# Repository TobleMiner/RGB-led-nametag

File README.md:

RGB LED nametag
===============

While there are a few commercially available LED nametags out there they
are usually either monochrome only or far too big and bulky to wear.  
This project aims at designing a device solving that problem.  
At only 84mm wide and 29mm tall it is hardly any larger than normal,
boring paper nametags and packs a whole lot more features:

- WLAN enabled
- 48x16 glorious RGB led pixels with more than 16 million colors each
- Powerful ARM Cortex M7 and Xtensa 32bit dual core
- 3MB of onboard data storage

# Principle of operation

The RGB LEDs on this nametag are common anode LEDs. The LEDs are divided
into groups of 16 columns each. The display is then multiplexed over those
16 columns, always driving one of the 16 columns in each of the three
groups simultaneously. Each of the 3 groups features 48 low side row
drivers driving the R, G and B emitter of all 16 LEDs in the currently
selected column.  
Both the low and high side drivers are designed as shift registers. The
low side drivers are fed with data from a regular SPI while the high side
drivers are connected to a QSPI interface. On the QSPI interface three
of the four data lines are utilized to provide data for all three LED
groups simultaneously.  
Both the SPI and QSPI are peripherals of an STM32F722 MCU. The STM32
takes care of LED multiplexing, power management, user io and USB.  
To provide WLAN connectivity an ESP32 is connected to the STM32 via
an IRQ line, a SPI interface, an I2C interface and a UART. IO0 and EN of
the ESP32 are also connected to the STM32. This allows the STM32 to be
used as a USB to UART bridge allowing normal programming of the ESP32
directly from your favourite IDE.

# Assembly

Since double sided assembly and boards with blind vias tends to be on the
expensive side this project is comprised of four boards. The first one is
the board shown above. The remaining three boards are all the same and
carry 16x16 LEDs each. They need to be soldered back to back onto the
mainboard. Design files for the LED carrier boards can be found
[here](https://github.com/TobleMiner/16x16-RGB-led-panel).

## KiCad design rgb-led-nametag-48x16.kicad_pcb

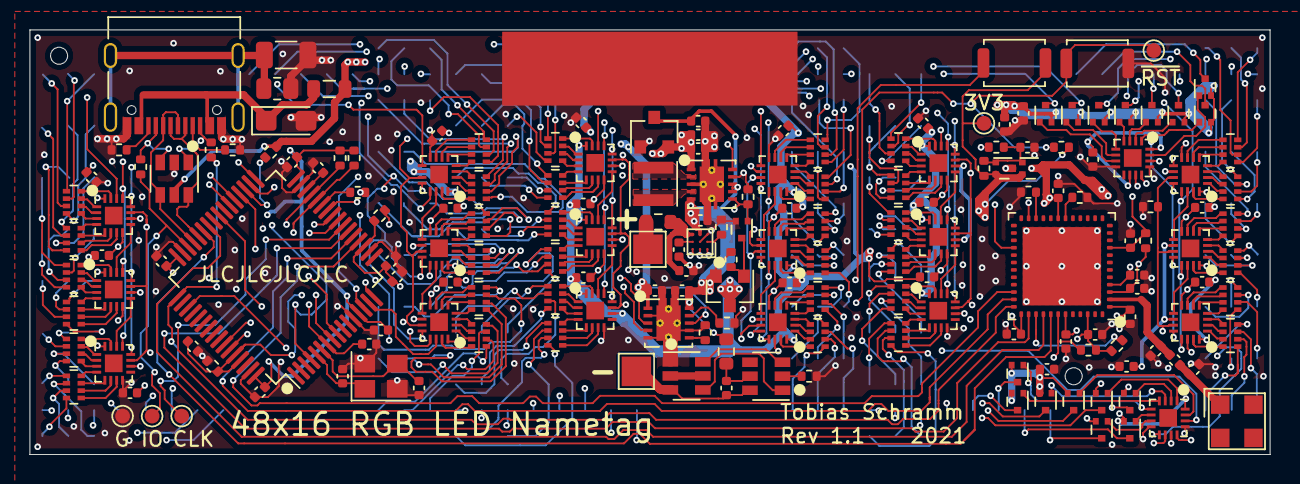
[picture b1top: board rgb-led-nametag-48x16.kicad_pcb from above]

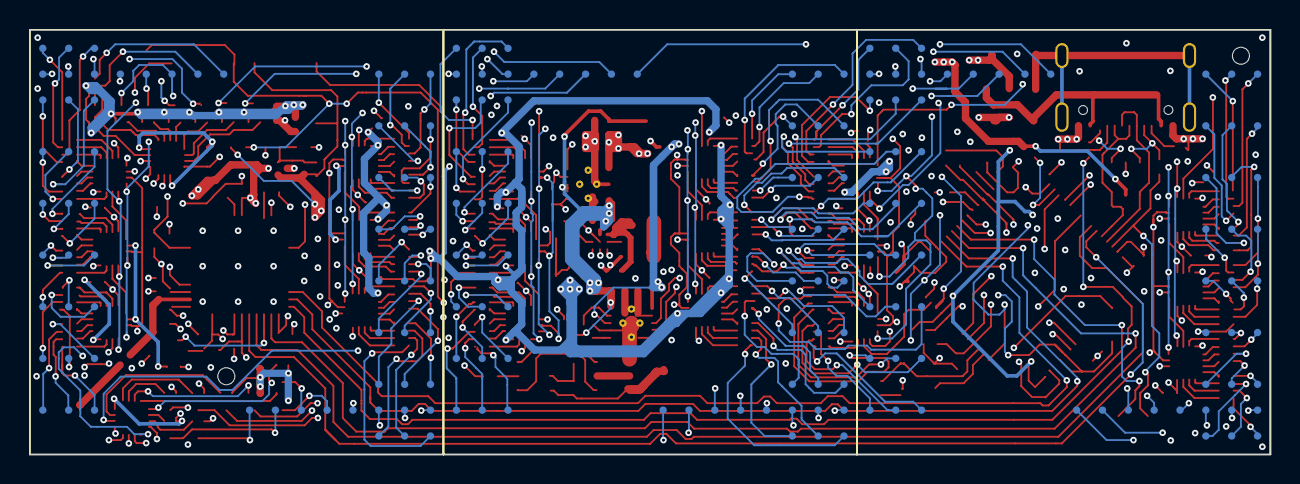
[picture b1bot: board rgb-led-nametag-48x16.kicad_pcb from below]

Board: 4 copper layers, 84.0 x 28.8 mm, 189 parts (3 on the bottom side), 405 nets.

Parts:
AE1: Antenna; 2065130001
C1, C2, C3, C4, C5, C6, C7, C8, C9, C10, C11, C12, C13, C14, C15, C16, C17, C18, C19, C20, C30, C32, C33, C34, C35, C36, C40, C46, C48, C49: 100nF; C_0402_1005Metric
C21, C22, C23, C24, C28, C29, C39, C41, C42, C43, C50, C51, C52: 10uF; C_0402_1005Metric
C25: 0R; C_0402_1005Metric
C26, C27: DNP; C_0402_1005Metric
C31: 4.7uF; C_0402_1005Metric
C37: 1nF; C_1206_3216Metric
C38: 10uF; CP_EIA-3216-10_Kemet-I
C44, C45, C47, C53, C54: 1uF; C_0402_1005Metric
C55, C56: 20pF; C_0402_1005Metric
F1: 4A; R_0603_1608Metric
FB1: Bead; L_0805_2012Metric
H1, H2: ToolingHole; ToolingHole_JLCSMT
H3: Safety pin; MountingPad_20x5mm
J1: USB_C_Receptacle_USB2.0; USB_C_Receptacle_Palconn_UTC16-G
L1: 2.2uH; L_Taiyo-Yuden_MD-3030
Q1, Q2, Q3, Q4, Q5, Q6, Q7, Q8, Q9, Q10, Q11, Q12, Q13, Q14, Q15, Q16, Q17, Q18: CJ3139K; SOT-723
Q19: 2SK3541; SOT-723
Q20: AO3401A; SOT-23
Q21: FS8205A; SOT-23-6
R1, R2, R6, R10, R12: 100k; R_0402_1005Metric
R3: 200k; R_0805_2012Metric
R4, R5, R13, R14, R17, R18, R19, R25, R26: 5.1k; R_0402_1005Metric
R7, R15, R16: 470R; R_0402_1005Metric
R8: 33R; R_0402_1005Metric
R9, R21, R23, R24, R27: 10k; R_0402_1005Metric
R11: 1k; R_0402_1005Metric
R20: 1.5k; R_0402_1005Metric
R22: 470R; R_0603_1608Metric
RN1, RN2, RN3, RN4, RN5, RN6, RN7, RN8, RN9, RN10, RN11, RN12, RN13, RN14, RN15, RN16, RN17, RN18, RN19, RN20, RN21, RN22, RN23, RN24, RN25, RN26, RN27, RN28, RN29, RN30, RN31, RN32, RN33, RN34, RN35, RN36: 220R; R_Array_Concave_4x0402
SW1: DFU/BTN; SW_Push_SPST_NO_Alps_SKRK
SW2: RST; SW_Push_SPST_NO_Alps_SKRK
TP1: BAT+; TestPoint_Pad_2.0x2.0mm
TP2: BAT-; TestPoint_Pad_2.0x2.0mm
TP3: ~{RST}; TestPoint_Pad_D1.0mm
TP4: SWDIO; TestPoint_Pad_D1.0mm
TP5: SWCLK; TestPoint_Pad_D1.0mm
TP6: GND; TestPoint_Pad_D1.0mm
TP7: 3V3; TestPoint_Pad_D1.0mm
U1, U9, U16: led-panel-16x16; bga-led-panel-16x16
U2, U3, U4, U5, U6, U7, U8, U10, U11, U12, U13, U14, U15, U17, U18, U19, U20, U21, U22, U23: 74HC595; X1QFN-16-2.5x2.5-EP-1.2
U24: ESP32-PICO-D4; ESP32-Pico-D4
U25: STM32F722RETx; LQFP-64_10x10mm_P0.5mm
U26: SRV05-4; SOT-23-6
U27: TPS63001; Texas_DRC0010J_ThermalVias
U28: XC6206P332MR; SOT-23
U29: BQ24081; Texas_DRC0010J_ThermalVias
U30: DW01+G; SOT-23-6
U31: BQ27421; DSBGA-9_1.6x1.6_P0.5mm
Y1: 16MHz; Crystal_SMD_3225-4Pin_3.2x2.5mm

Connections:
+3V3: C32.1, C33.2, C34.1, C35.1, C36.1, C42.2, C43.2, C50.1, Q17.2 (S), Q18.2 (S), R1.2, R10.2, R25.2, R26.1, R27.2, SW1.2, TP7.1, U25.13 (VREF+), U25.19 (VDD), U25.32 (VDD), U25.48 (VDD), U25.64 (VDD), U27.1 (VOUT), U27.10 (FB), U28.2 (VO)
+5V: C47.1, FB1.1, R23.2, U26.5 (VP), U29.1 (IN), U29.8 (~TE)
+BATT: C41.2, C44.1, C48.2, Q20.2 (S), R12.1, R22.1, U27.5 (VIN), U27.7 (PS/SYNC), U27.8 (VINA), U28.3 (VI), U29.10 (OUT), U31.C2 (SRX)
/A1: Q1.3 (D), U1.B1 (A1), U9.B1 (A1), U16.B1 (A1)
/A2: Q2.3 (D), U1.B2 (A2), U9.B2 (A2), U16.B2 (A2)
/A3: Q3.3 (D), U1.B3 (A3), U9.B3 (A3), U16.B3 (A3)
/A4: Q4.3 (D), U1.B4 (A4), U9.B4 (A4), U16.B4 (A4)
/A5: Q5.3 (D), U1.B5 (A5), U9.B5 (A5), U16.B5 (A5)
/A6: Q6.3 (D), U1.B6 (A6), U9.B6 (A6), U16.B6 (A6)
/A7: Q7.3 (D), U1.B7 (A7), U9.B7 (A7), U16.B7 (A7)
/A8: Q8.3 (D), U1.B8 (A8), U9.B8 (A8), U16.B8 (A8)
/A9: Q9.3 (D), U1.R9 (A9), U9.R9 (A9), U16.R9 (A9)
/A10: Q10.3 (D), U1.R10 (A10), U9.R10 (A10), U16.R10 (A10)
/A11: Q11.3 (D), U1.R11 (A11), U9.R11 (A11), U16.R11 (A11)
/A12: Q12.3 (D), U1.R12 (A12), U9.R12 (A12), U16.R12 (A12)
/A13: Q13.3 (D), U1.R13 (A13), U9.R13 (A13), U16.R13 (A13)
/A14: Q14.3 (D), U1.R14 (A14), U9.R14 (A14), U16.R14 (A14)
/A15: Q15.3 (D), U1.R15 (A15), U9.R15 (A15), U16.R15 (A15)
/A16: Q16.3 (D), U1.R16 (A16), U9.R16 (A16), U16.R16 (A16)
/BOOT: U24.23 (IO0), U25.25 (PB0)
/COL_LATCH: U8.12 (RCLK), U23.12 (RCLK), U25.14 (PA0)
/D+: J1.A6 (D+), J1.B6 (D+), U25.45 (PA12), U26.4 (IO3)
/D-: J1.A7 (D-), J1.B7 (D-), U25.44 (PA11), U26.6 (IO4)
/DFU: C46.1, R2.2, SW1.1, U25.60 (BOOT0), U25.61 (PB8)
/EN: C40.1, R6.1, U24.9 (EN), U25.26 (PB1)
/GAUGE_SCL: R25.1, U25.28 (PB10), U31.A3 (SCL)
/GAUGE_SDA: R26.2, U25.29 (PB11), U31.A2 (SDA)
/GPOUT: R27.1, U25.9 (PC1), U31.A1 (GPOUT)
/High side 1/SOUT: U8.9 (QH'), U23.14 (SER)
/IRQ: U24.28 (SD2/IO9), U25.24 (PC4)
/L1: L1.1, U27.4 (L1)
/L2: L1.2, U27.2 (L2)
/PWR_EN: Q19.1 (G), R9.1, U25.4 (PC15), U27.6 (EN)
/Panel 1/B1: RN2.2 (R2.1), U1.A3 (B1)
/Panel 1/B2: RN11.3 (R3.1), U1.B16 (B2)
/Panel 1/B3: RN1.3 (R3.1), U1.C3 (B3)
/Panel 1/B4: RN12.2 (R2.1), U1.D16 (B4)
/Panel 1/B5: RN4.4 (R4.1), U1.E3 (B5)
/Panel 1/B6: RN9.1 (R1.1), U1.F16 (B6)
/Panel 1/B7: RN4.1 (R1.1), U1.G3 (B7)
/Panel 1/B8: RN9.4 (R4.1), U1.H16 (B8)
/Panel 1/B9: RN3.2 (R2.1), U1.J3 (B9)
/Panel 1/B10: RN10.3 (R3.1), U1.K16 (B10)
/Panel 1/B11: RN6.3 (R3.1), U1.L3 (B11)
/Panel 1/B12: RN7.2 (R2.1), U1.M16 (B12)
/Panel 1/B13: RN5.4 (R4.1), U1.N3 (B13)
/Panel 1/B14: RN8.1 (R1.1), U1.P16 (B14)
/Panel 1/B15: RN5.1 (R1.1), U1.R3 (B15)
/Panel 1/B16: RN8.4 (R4.1), U1.T16 (B16)
/Panel 1/G1: RN2.3 (R3.1), U1.A2 (G1)
/Panel 1/G2: RN11.2 (R2.1), U1.B15 (G2)
/Panel 1/G3: RN1.4 (R4.1), U1.C2 (G3)
/Panel 1/G4: RN12.1 (R1.1), U1.D15 (G4)
/Panel 1/G5: RN1.1 (R1.1), U1.E2 (G5)
/Panel 1/G6: RN12.4 (R4.1), U1.F15 (G6)
/Panel 1/G7: RN4.2 (R2.1), U1.G2 (G7)
/Panel 1/G8: RN9.3 (R3.1), U1.H15 (G8)
/Panel 1/G9: RN3.3 (R3.1), U1.J2 (G9)
/Panel 1/G10: RN10.2 (R2.1), U1.K15 (G10)
/Panel 1/G11: RN6.4 (R4.1), U1.L2 (G11)
/Panel 1/G12: RN7.1 (R1.1), U1.M15 (G12)
/Panel 1/G13: RN6.1 (R1.1), U1.N2 (G13)
/Panel 1/G14: RN7.4 (R4.1), U1.P15 (G14)
/Panel 1/G15: RN5.2 (R2.1), U1.R2 (G15)
/Panel 1/G16: RN8.3 (R3.1), U1.T15 (G16)
/Panel 1/R1: RN2.4 (R4.1), U1.A1 (R1)
/Panel 1/R2: RN11.1 (R1.1), U1.B14 (R2)
/Panel 1/R3: RN2.1 (R1.1), U1.C1 (R3)
/Panel 1/R4: RN11.4 (R4.1), U1.D14 (R4)
/Panel 1/R5: RN1.2 (R2.1), U1.E1 (R5)
/Panel 1/R6: RN12.3 (R3.1), U1.F14 (R6)
/Panel 1/R7: RN4.3 (R3.1), U1.G1 (R7)
/Panel 1/R8: RN9.2 (R2.1), U1.H14 (R8)
/Panel 1/R9: RN3.4 (R4.1), U1.J1 (R9)
/Panel 1/R10: RN10.1 (R1.1), U1.K14 (R10)
/Panel 1/R11: RN3.1 (R1.1), U1.L1 (R11)
/Panel 1/R12: RN10.4 (R4.1), U1.M14 (R12)
/Panel 1/R13: RN6.2 (R2.1), U1.N1 (R13)
/Panel 1/R14: RN7.3 (R3.1), U1.P14 (R14)
/Panel 1/R15: RN5.3 (R3.1), U1.R1 (R15)
/Panel 1/R16: RN8.2 (R2.1), U1.T14 (R16)
/Panel 1/Sheet61A5C766/SIN: U2.14 (SER), U3.9 (QH')
/Panel 1/sheet61A6C351/SIN: U4.14 (SER), U5.9 (QH')
/Panel 1/sheet61A68DA0/SIN: U3.14 (SER), U4.9 (QH')
/Panel 1/sheet61A75B3A/SIN: U6.14 (SER), U7.9 (QH')
/Panel 1/sheet61A75B39/SIN: U5.14 (SER), U6.9 (QH')
/Panel 2/B1: RN14.2 (R2.1), U9.A3 (B1)
/Panel 2/B2: RN23.3 (R3.1), U9.B16 (B2)
/Panel 2/B3: RN13.3 (R3.1), U9.C3 (B3)
/Panel 2/B4: RN24.2 (R2.1), U9.D16 (B4)
/Panel 2/B5: RN16.4 (R4.1), U9.E3 (B5)
/Panel 2/B6: RN21.1 (R1.1), U9.F16 (B6)
/Panel 2/B7: RN16.1 (R1.1), U9.G3 (B7)
/Panel 2/B8: RN21.4 (R4.1), U9.H16 (B8)
/Panel 2/B9: RN15.2 (R2.1), U9.J3 (B9)
/Panel 2/B10: RN22.3 (R3.1), U9.K16 (B10)
/Panel 2/B11: RN18.3 (R3.1), U9.L3 (B11)
/Panel 2/B12: RN19.2 (R2.1), U9.M16 (B12)
/Panel 2/B13: RN17.4 (R4.1), U9.N3 (B13)
/Panel 2/B14: RN20.1 (R1.1), U9.P16 (B14)
/Panel 2/B15: RN17.1 (R1.1), U9.R3 (B15)
/Panel 2/B16: RN20.4 (R4.1), U9.T16 (B16)
/Panel 2/G1: RN14.3 (R3.1), U9.A2 (G1)
/Panel 2/G2: RN23.2 (R2.1), U9.B15 (G2)
/Panel 2/G3: RN13.4 (R4.1), U9.C2 (G3)
/Panel 2/G4: RN24.1 (R1.1), U9.D15 (G4)
/Panel 2/G5: RN13.1 (R1.1), U9.E2 (G5)
/Panel 2/G6: RN24.4 (R4.1), U9.F15 (G6)
/Panel 2/G7: RN16.2 (R2.1), U9.G2 (G7)
/Panel 2/G8: RN21.3 (R3.1), U9.H15 (G8)
/Panel 2/G9: RN15.3 (R3.1), U9.J2 (G9)
/Panel 2/G10: RN22.2 (R2.1), U9.K15 (G10)
/Panel 2/G11: RN18.4 (R4.1), U9.L2 (G11)
/Panel 2/G12: RN19.1 (R1.1), U9.M15 (G12)
/Panel 2/G13: RN18.1 (R1.1), U9.N2 (G13)
/Panel 2/G14: RN19.4 (R4.1), U9.P15 (G14)
/Panel 2/G15: RN17.2 (R2.1), U9.R2 (G15)
/Panel 2/G16: RN20.3 (R3.1), U9.T15 (G16)
/Panel 2/R1: RN14.4 (R4.1), U9.A1 (R1)
/Panel 2/R2: RN23.1 (R1.1), U9.B14 (R2)
/Panel 2/R3: RN14.1 (R1.1), U9.C1 (R3)
/Panel 2/R4: RN23.4 (R4.1), U9.D14 (R4)
/Panel 2/R5: RN13.2 (R2.1), U9.E1 (R5)
/Panel 2/R6: RN24.3 (R3.1), U9.F14 (R6)
/Panel 2/R7: RN16.3 (R3.1), U9.G1 (R7)
/Panel 2/R8: RN21.2 (R2.1), U9.H14 (R8)
/Panel 2/R9: RN15.4 (R4.1), U9.J1 (R9)
/Panel 2/R10: RN22.1 (R1.1), U9.K14 (R10)
/Panel 2/R11: RN15.1 (R1.1), U9.L1 (R11)
/Panel 2/R12: RN22.4 (R4.1), U9.M14 (R12)
/Panel 2/R13: RN18.2 (R2.1), U9.N1 (R13)
/Panel 2/R14: RN19.3 (R3.1), U9.P14 (R14)
/Panel 2/R15: RN17.3 (R3.1), U9.R1 (R15)
/Panel 2/R16: RN20.2 (R2.1), U9.T14 (R16)
/Panel 2/Sheet61A5C766/SIN: U10.14 (SER), U11.9 (QH')
/Panel 2/sheet61A6C351/SIN: U12.14 (SER), U13.9 (QH')
/Panel 2/sheet61A68DA0/SIN: U11.14 (SER), U12.9 (QH')
/Panel 2/sheet61A75B3A/SIN: U14.14 (SER), U15.9 (QH')
/Panel 2/sheet61A75B39/SIN: U13.14 (SER), U14.9 (QH')
/Panel 3/B1: RN26.2 (R2.1), U16.A3 (B1)
/Panel 3/B2: RN35.3 (R3.1), U16.B16 (B2)
/Panel 3/B3: RN25.3 (R3.1), U16.C3 (B3)
/Panel 3/B4: RN36.2 (R2.1), U16.D16 (B4)
/Panel 3/B5: RN28.4 (R4.1), U16.E3 (B5)
/Panel 3/B6: RN33.1 (R1.1), U16.F16 (B6)
/Panel 3/B7: RN28.1 (R1.1), U16.G3 (B7)
/Panel 3/B8: RN33.4 (R4.1), U16.H16 (B8)
/Panel 3/B9: RN27.2 (R2.1), U16.J3 (B9)
/Panel 3/B10: RN34.3 (R3.1), U16.K16 (B10)
/Panel 3/B11: RN30.3 (R3.1), U16.L3 (B11)
/Panel 3/B12: RN31.2 (R2.1), U16.M16 (B12)
/Panel 3/B13: RN29.4 (R4.1), U16.N3 (B13)
/Panel 3/B14: RN32.1 (R1.1), U16.P16 (B14)
/Panel 3/B15: RN29.1 (R1.1), U16.R3 (B15)
/Panel 3/B16: RN32.4 (R4.1), U16.T16 (B16)
/Panel 3/G1: RN26.3 (R3.1), U16.A2 (G1)
/Panel 3/G2: RN35.2 (R2.1), U16.B15 (G2)
/Panel 3/G3: RN25.4 (R4.1), U16.C2 (G3)
/Panel 3/G4: RN36.1 (R1.1), U16.D15 (G4)
/Panel 3/G5: RN25.1 (R1.1), U16.E2 (G5)
/Panel 3/G6: RN36.4 (R4.1), U16.F15 (G6)
/Panel 3/G7: RN28.2 (R2.1), U16.G2 (G7)
/Panel 3/G8: RN33.3 (R3.1), U16.H15 (G8)
/Panel 3/G9: RN27.3 (R3.1), U16.J2 (G9)
/Panel 3/G10: RN34.2 (R2.1), U16.K15 (G10)
/Panel 3/G11: RN30.4 (R4.1), U16.L2 (G11)
/Panel 3/G12: RN31.1 (R1.1), U16.M15 (G12)
/Panel 3/G13: RN30.1 (R1.1), U16.N2 (G13)
/Panel 3/G14: RN31.4 (R4.1), U16.P15 (G14)
/Panel 3/G15: RN29.2 (R2.1), U16.R2 (G15)
/Panel 3/G16: RN32.3 (R3.1), U16.T15 (G16)
/Panel 3/R1: RN26.4 (R4.1), U16.A1 (R1)
/Panel 3/R2: RN35.1 (R1.1), U16.B14 (R2)
/Panel 3/R3: RN26.1 (R1.1), U16.C1 (R3)
/Panel 3/R4: RN35.4 (R4.1), U16.D14 (R4)
/Panel 3/R5: RN25.2 (R2.1), U16.E1 (R5)
/Panel 3/R6: RN36.3 (R3.1), U16.F14 (R6)
/Panel 3/R7: RN28.3 (R3.1), U16.G1 (R7)
/Panel 3/R8: RN33.2 (R2.1), U16.H14 (R8)
/Panel 3/R9: RN27.4 (R4.1), U16.J1 (R9)
/Panel 3/R10: RN34.1 (R1.1), U16.K14 (R10)
/Panel 3/R11: RN27.1 (R1.1), U16.L1 (R11)
/Panel 3/R12: RN34.4 (R4.1), U16.M14 (R12)
/Panel 3/R13: RN30.2 (R2.1), U16.N1 (R13)
/Panel 3/R14: RN31.3 (R3.1), U16.P14 (R14)
/Panel 3/R15: RN29.3 (R3.1), U16.R1 (R15)
/Panel 3/R16: RN32.2 (R2.1), U16.T14 (R16)
/Panel 3/Sheet61A5C766/SIN: U17.14 (SER), U18.9 (QH')
/Panel 3/sheet61A6C351/SIN: U19.14 (SER), U20.9 (QH')
/Panel 3/sheet61A68DA0/SIN: U18.14 (SER), U19.9 (QH')
/Panel 3/sheet61A75B3A/SIN: U21.14 (SER), U22.9 (QH')
/Panel 3/sheet61A75B39/SIN: U20.14 (SER), U21.9 (QH')
/QSPI_CLK: R7.2, R8.1, U2.11 (SRCLK), U3.11 (SRCLK), U4.11 (SRCLK), U5.11 (SRCLK), U6.11 (SRCLK), U7.11 (SRCLK), U10.11 (SRCLK), U11.11 (SRCLK), U12.11 (SRCLK), U13.11 (SRCLK), U14.11 (SRCLK), U15.11 (SRCLK), U17.11 (SRCLK), U18.11 (SRCLK), U19.11 (SRCLK), U20.11 (SRCLK), U21.11 (SRCLK), U22.11 (SRCLK)
/QSPI_D0: U15.14 (SER), U25.40 (PC9)
/QSPI_D1: U22.14 (SER), U25.51 (PC10)
/QSPI_D3: U7.14 (SER), U25.15 (PA1)
/ROW_LATCH: U2.12 (RCLK), U3.12 (RCLK), U4.12 (RCLK), U5.12 (RCLK), U6.12 (RCLK), U7.12 (RCLK), U10.12 (RCLK), U11.12 (RCLK), U12.12 (RCLK), U13.12 (RCLK), U14.12 (RCLK), U15.12 (RCLK), U17.12 (RCLK), U18.12 (RCLK), U19.12 (RCLK), U20.12 (RCLK), U21.12 (RCLK), U22.12 (RCLK), U25.37 (PC6)
/ROW_~OE: U2.13 (~OE), U3.13 (~OE), U4.13 (~OE), U5.13 (~OE), U6.13 (~OE), U7.13 (~OE), U10.13 (~OE), U11.13 (~OE), U12.13 (~OE), U13.13 (~OE), U14.13 (~OE), U15.13 (~OE), U17.13 (~OE), U18.13 (~OE), U19.13 (~OE), U20.13 (~OE), U21.13 (~OE), U22.13 (~OE), U25.38 (PC7)
/RX: U24.41 (U0TXD/IO1), U25.43 (PA10)
/SCL: R14.2, U24.39 (IO22), U25.58 (PB6)
/SDA: R13.2, U24.42 (IO21), U25.59 (PB7)
/SPI1_CLK: U24.35 (IO18), U25.21 (PA5)
/SPI1_MISO: U24.38 (IO19), U25.22 (PA6)
/SPI1_MOSI: U24.36 (IO23), U25.23 (PA7)
/SPI1_~CS: U24.34 (IO5), U25.20 (PA4)
/SPI2_CLK: U8.11 (SRCLK), U23.11 (SRCLK), U25.34 (PB13)
/SPI2_MOSI: U8.14 (SER), U25.36 (PB15)
/SWCLK: R16.2, TP5.1, U25.49 (PA14)
/SWCLK_SBU: J1.B8 (SBU2), R16.1, U26.1 (IO1)
/SWDIO: R15.1, TP4.1, U25.46 (PA13)
/SWDIO_SBU: J1.A8 (SBU1), R15.2, U26.3 (IO2)
/Sheet620161B9/3V3: C21.2, C22.2, C23.2, C24.2, C28.2, C29.2, C39.2, Q17.3 (D), Q18.3 (D), R6.2, R13.1, R14.1, U24.1 (VDDA), U24.3 (VDDA3P3), U24.4 (VDDA3P3), U24.19 (VDD3P3_RTC), U24.37 (VDD3P3_CPU), U24.43 (VDDA), U24.46 (VDDA)
/Sheet620161B9/HSPIQ: R19.1, U24.18 (IO12)
/TX: U24.40 (U0RXD/IO3), U25.42 (PA9)
/USB_SENSE: R23.1, U25.35 (PB14)
/~CHRG: U25.8 (PC0), U29.3 (STAT1)
/~ESP_EN: R17.1, U25.33 (PB12)
/~RST: C30.1, R1.1, SW2.1, TP3.1, U25.7 (NRST)
/~STAT2: U25.16 (PA2), U29.4 (STAT2)
GND: C1.1, C2.1, C3.1, C4.1, C5.1, C6.1, C7.1, C8.1, C9.1, C10.1, C11.1, C12.1, C13.1, C14.1, C15.1, C16.1, C17.1, C18.1, C19.1, C20.1, C21.1, C22.1, C23.1, C24.1, C26.2, C27.1, C28.1, C29.1, C30.2, C31.2, C32.2, C33.1, C34.2, C35.2, C36.2, C37.1, C38.2, C39.1, C40.2, C41.1, C42.1, C43.1, C44.2, C45.2, C46.2, C47.2, C48.1, C50.2, C51.2, C52.2, C53.2, C54.1, C55.2, C56.1, H3.1, J1.A1 (GND), J1.A12 (GND), J1.B1 (GND), J1.B12 (GND), Q19.2 (S), Q21.1, R2.1, R3.1, R4.2, R5.1, R7.1, R9.2, R11.2, R18.2, R19.2, R20.1, R21.2, R24.1, SW2.2, TP6.1, U2.8 (GND), U3.8 (GND), U4.8 (GND), U5.8 (GND), U6.8 (GND), U7.8 (GND), U8.8 (GND), U8.13 (~OE), U10.8 (GND), U11.8 (GND), U12.8 (GND), U13.8 (GND), U14.8 (GND), U15.8 (GND), U17.8 (GND), U18.8 (GND), U19.8 (GND), U20.8 (GND), U21.8 (GND), U22.8 (GND), U23.8 (GND), U23.13 (~OE), U24.49 (GND), U25.12 (VSSA), U25.18 (VSS), U25.31 (VSS), U25.47 (VSS), U25.63 (VSS), U26.2 (VN), U27.3 (PGND), U27.9 (GND), U27.11 (PGND), U28.1 (GND), U29.2 (GND), U29.5 (GND), U29.7 (GND), U29.11 (GND), U31.B2 (VSS), U31.C1 (VSS), Y1.2, Y1.4
unnamed: AE1.1 (A), C25.1, C26.1
unnamed: C25.2, C27.2, U24.2 (LNA_IN)
unnamed: C31.1, U25.30 (VCAP_1)
unnamed: C37.2, J1.S1 (SHIELD), R3.2
unnamed: C38.1, FB1.2, J1.A4 (VBUS), J1.A9 (VBUS), J1.B4 (VBUS), J1.B9 (VBUS)
unnamed: C45.1, Q17.1 (G), Q18.1 (G), R10.1, R17.2
unnamed: C49.1, Q21.3, TP2.1, U30.6 (VSS)
unnamed: C49.2, R22.2, U30.5 (VDD)
unnamed: C53.1, F1.2, U31.C3 (BAT)
unnamed: C54.2, U31.B3 (VDD)
unnamed: C55.1, U25.5 (PH0), Y1.1
unnamed: C56.2, U25.6 (PH1), Y1.3
unnamed: F1.1, TP1.1
unnamed: J1.A5 (CC1), R4.1
unnamed: J1.B5 (CC2), R5.2
unnamed: Q1.1 (G), U8.15 (QA)
unnamed: Q2.1 (G), U8.1 (QB)
unnamed: Q3.1 (G), U8.2 (QC)
unnamed: Q4.1 (G), U8.3 (QD)
unnamed: Q5.1 (G), U8.4 (QE)
unnamed: Q6.1 (G), U8.5 (QF)
unnamed: Q7.1 (G), U8.6 (QG)
unnamed: Q8.1 (G), U8.7 (QH)
unnamed: Q9.1 (G), U23.15 (QA)
unnamed: Q10.1 (G), U23.1 (QB)
unnamed: Q11.1 (G), U23.2 (QC)
unnamed: Q12.1 (G), U23.3 (QD)
unnamed: Q13.1 (G), U23.4 (QE)
unnamed: Q14.1 (G), U23.5 (QF)
unnamed: Q15.1 (G), U23.6 (QG)
unnamed: Q16.1 (G), U23.7 (QH)
unnamed: Q19.3 (D), Q20.1 (G), R12.2
unnamed: Q21.4, U30.1 (DO)
unnamed: Q21.6, U30.3 (CO)
unnamed: R11.1, U30.2 (VM)
unnamed: R18.1, U24.22 (IO2)
unnamed: R20.2, U29.6 (ISET)
unnamed: R21.1, U29.9 (TS)
unnamed: R24.2, U31.B1 (BIN)
unnamed: RN1.5 (R4.2), U2.3 (QD)
unnamed: RN1.6 (R3.2), U2.2 (QC)
unnamed: RN1.7 (R2.2), U2.1 (QB)
unnamed: RN1.8 (R1.2), U2.15 (QA)
unnamed: RN2.5 (R4.2), U2.7 (QH)
unnamed: RN2.6 (R3.2), U2.6 (QG)
unnamed: RN2.7 (R2.2), U2.5 (QF)
unnamed: RN2.8 (R1.2), U2.4 (QE)
unnamed: RN3.5 (R4.2), U3.3 (QD)
unnamed: RN3.6 (R3.2), U3.2 (QC)
unnamed: RN3.7 (R2.2), U3.1 (QB)
unnamed: RN3.8 (R1.2), U3.15 (QA)
unnamed: RN4.5 (R4.2), U3.7 (QH)
unnamed: RN4.6 (R3.2), U3.6 (QG)
unnamed: RN4.7 (R2.2), U3.5 (QF)
unnamed: RN4.8 (R1.2), U3.4 (QE)
unnamed: RN5.5 (R4.2), U4.3 (QD)
unnamed: RN5.6 (R3.2), U4.2 (QC)
unnamed: RN5.7 (R2.2), U4.1 (QB)
unnamed: RN5.8 (R1.2), U4.15 (QA)
unnamed: RN6.5 (R4.2), U4.7 (QH)
unnamed: RN6.6 (R3.2), U4.6 (QG)
unnamed: RN6.7 (R2.2), U4.5 (QF)
unnamed: RN6.8 (R1.2), U4.4 (QE)
unnamed: RN7.5 (R4.2), U5.3 (QD)
unnamed: RN7.6 (R3.2), U5.2 (QC)
unnamed: RN7.7 (R2.2), U5.1 (QB)
unnamed: RN7.8 (R1.2), U5.15 (QA)
unnamed: RN8.5 (R4.2), U5.7 (QH)
unnamed: RN8.6 (R3.2), U5.6 (QG)
unnamed: RN8.7 (R2.2), U5.5 (QF)
unnamed: RN8.8 (R1.2), U5.4 (QE)
unnamed: RN9.5 (R4.2), U6.3 (QD)
unnamed: RN9.6 (R3.2), U6.2 (QC)
unnamed: RN9.7 (R2.2), U6.1 (QB)
unnamed: RN9.8 (R1.2), U6.15 (QA)
unnamed: RN10.5 (R4.2), U6.7 (QH)
unnamed: RN10.6 (R3.2), U6.6 (QG)
unnamed: RN10.7 (R2.2), U6.5 (QF)
unnamed: RN10.8 (R1.2), U6.4 (QE)
unnamed: RN11.5 (R4.2), U7.3 (QD)
unnamed: RN11.6 (R3.2), U7.2 (QC)
unnamed: RN11.7 (R2.2), U7.1 (QB)
unnamed: RN11.8 (R1.2), U7.15 (QA)
unnamed: RN12.5 (R4.2), U7.7 (QH)
unnamed: RN12.6 (R3.2), U7.6 (QG)
unnamed: RN12.7 (R2.2), U7.5 (QF)
unnamed: RN12.8 (R1.2), U7.4 (QE)
unnamed: RN13.5 (R4.2), U10.3 (QD)
unnamed: RN13.6 (R3.2), U10.2 (QC)
unnamed: RN13.7 (R2.2), U10.1 (QB)
unnamed: RN13.8 (R1.2), U10.15 (QA)
unnamed: RN14.5 (R4.2), U10.7 (QH)
unnamed: RN14.6 (R3.2), U10.6 (QG)
unnamed: RN14.7 (R2.2), U10.5 (QF)
unnamed: RN14.8 (R1.2), U10.4 (QE)
unnamed: RN15.5 (R4.2), U11.3 (QD)
unnamed: RN15.6 (R3.2), U11.2 (QC)
unnamed: RN15.7 (R2.2), U11.1 (QB)
unnamed: RN15.8 (R1.2), U11.15 (QA)
unnamed: RN16.5 (R4.2), U11.7 (QH)
unnamed: RN16.6 (R3.2), U11.6 (QG)
unnamed: RN16.7 (R2.2), U11.5 (QF)
unnamed: RN16.8 (R1.2), U11.4 (QE)
unnamed: RN17.5 (R4.2), U12.3 (QD)
unnamed: RN17.6 (R3.2), U12.2 (QC)
unnamed: RN17.7 (R2.2), U12.1 (QB)
unnamed: RN17.8 (R1.2), U12.15 (QA)
unnamed: RN18.5 (R4.2), U12.7 (QH)
unnamed: RN18.6 (R3.2), U12.6 (QG)
unnamed: RN18.7 (R2.2), U12.5 (QF)
unnamed: RN18.8 (R1.2), U12.4 (QE)
unnamed: RN19.5 (R4.2), U13.3 (QD)
unnamed: RN19.6 (R3.2), U13.2 (QC)
unnamed: RN19.7 (R2.2), U13.1 (QB)
unnamed: RN19.8 (R1.2), U13.15 (QA)
unnamed: RN20.5 (R4.2), U13.7 (QH)
unnamed: RN20.6 (R3.2), U13.6 (QG)
unnamed: RN20.7 (R2.2), U13.5 (QF)
unnamed: RN20.8 (R1.2), U13.4 (QE)
unnamed: RN21.5 (R4.2), U14.3 (QD)
unnamed: RN21.6 (R3.2), U14.2 (QC)
unnamed: RN21.7 (R2.2), U14.1 (QB)
unnamed: RN21.8 (R1.2), U14.15 (QA)
unnamed: RN22.5 (R4.2), U14.7 (QH)
unnamed: RN22.6 (R3.2), U14.6 (QG)
unnamed: RN22.7 (R2.2), U14.5 (QF)
unnamed: RN22.8 (R1.2), U14.4 (QE)
unnamed: RN23.5 (R4.2), U15.3 (QD)
unnamed: RN23.6 (R3.2), U15.2 (QC)
unnamed: RN23.7 (R2.2), U15.1 (QB)
unnamed: RN23.8 (R1.2), U15.15 (QA)
unnamed: RN24.5 (R4.2), U15.7 (QH)
unnamed: RN24.6 (R3.2), U15.6 (QG)
unnamed: RN24.7 (R2.2), U15.5 (QF)
unnamed: RN24.8 (R1.2), U15.4 (QE)
unnamed: RN25.5 (R4.2), U17.3 (QD)
unnamed: RN25.6 (R3.2), U17.2 (QC)
unnamed: RN25.7 (R2.2), U17.1 (QB)
unnamed: RN25.8 (R1.2), U17.15 (QA)
unnamed: RN26.5 (R4.2), U17.7 (QH)
unnamed: RN26.6 (R3.2), U17.6 (QG)
unnamed: RN26.7 (R2.2), U17.5 (QF)
unnamed: RN26.8 (R1.2), U17.4 (QE)
unnamed: RN27.5 (R4.2), U18.3 (QD)
unnamed: RN27.6 (R3.2), U18.2 (QC)
unnamed: RN27.7 (R2.2), U18.1 (QB)
unnamed: RN27.8 (R1.2), U18.15 (QA)
unnamed: RN28.5 (R4.2), U18.7 (QH)
unnamed: RN28.6 (R3.2), U18.6 (QG)
unnamed: RN28.7 (R2.2), U18.5 (QF)
unnamed: RN28.8 (R1.2), U18.4 (QE)
unnamed: RN29.5 (R4.2), U19.3 (QD)
unnamed: RN29.6 (R3.2), U19.2 (QC)
unnamed: RN29.7 (R2.2), U19.1 (QB)
unnamed: RN29.8 (R1.2), U19.15 (QA)
unnamed: RN30.5 (R4.2), U19.7 (QH)
unnamed: RN30.6 (R3.2), U19.6 (QG)
unnamed: RN30.7 (R2.2), U19.5 (QF)
unnamed: RN30.8 (R1.2), U19.4 (QE)
unnamed: RN31.5 (R4.2), U20.3 (QD)
unnamed: RN31.6 (R3.2), U20.2 (QC)
unnamed: RN31.7 (R2.2), U20.1 (QB)
unnamed: RN31.8 (R1.2), U20.15 (QA)
unnamed: RN32.5 (R4.2), U20.7 (QH)
unnamed: RN32.6 (R3.2), U20.6 (QG)
unnamed: RN32.7 (R2.2), U20.5 (QF)
unnamed: RN32.8 (R1.2), U20.4 (QE)
unnamed: RN33.5 (R4.2), U21.3 (QD)
unnamed: RN33.6 (R3.2), U21.2 (QC)
unnamed: RN33.7 (R2.2), U21.1 (QB)
unnamed: RN33.8 (R1.2), U21.15 (QA)
unnamed: RN34.5 (R4.2), U21.7 (QH)
unnamed: RN34.6 (R3.2), U21.6 (QG)
unnamed: RN34.7 (R2.2), U21.5 (QF)
unnamed: RN34.8 (R1.2), U21.4 (QE)
unnamed: RN35.5 (R4.2), U22.3 (QD)
unnamed: RN35.6 (R3.2), U22.2 (QC)
unnamed: RN35.7 (R2.2), U22.1 (QB)
unnamed: RN35.8 (R1.2), U22.15 (QA)
unnamed: RN36.5 (R4.2), U22.7 (QH)
unnamed: RN36.6 (R3.2), U22.6 (QG)
unnamed: RN36.7 (R2.2), U22.5 (QF)
unnamed: RN36.8 (R1.2), U22.4 (QE)
unnamed: R8.2, U25.27 (PB2)
VBUS: C1.2, C2.2, C3.2, C4.2, C5.2, C6.2, C7.2, C8.2, C9.2, C10.2, C11.2, C12.2, C13.2, C14.2, C15.2, C16.2, C17.2, C18.2, C19.2, C20.2, C51.1, C52.1, Q1.2 (S), Q2.2 (S), Q3.2 (S), Q4.2 (S), Q5.2 (S), Q6.2 (S), Q7.2 (S), Q8.2 (S), Q9.2 (S), Q10.2 (S), Q11.2 (S), Q12.2 (S), Q13.2 (S), Q14.2 (S), Q15.2 (S), Q16.2 (S), Q20.3 (D), U2.10 (~SRCLR), U2.16 (VCC), U3.10 (~SRCLR), U3.16 (VCC), U4.10 (~SRCLR), U4.16 (VCC), U5.10 (~SRCLR), U5.16 (VCC), U6.10 (~SRCLR), U6.16 (VCC), U7.10 (~SRCLR), U7.16 (VCC), U8.10 (~SRCLR), U8.16 (VCC), U10.10 (~SRCLR), U10.16 (VCC), U11.10 (~SRCLR), U11.16 (VCC), U12.10 (~SRCLR), U12.16 (VCC), U13.10 (~SRCLR), U13.16 (VCC), U14.10 (~SRCLR), U14.16 (VCC), U15.10 (~SRCLR), U15.16 (VCC), U17.10 (~SRCLR), U17.16 (VCC), U18.10 (~SRCLR), U18.16 (VCC), U19.10 (~SRCLR), U19.16 (VCC), U20.10 (~SRCLR), U20.16 (VCC), U21.10 (~SRCLR), U21.16 (VCC), U22.10 (~SRCLR), U22.16 (VCC), U23.10 (~SRCLR), U23.16 (VCC)

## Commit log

2021-11-28 Finish anode driver 1-8 layout
2021-11-28 Add driver bypassing
2021-12-06 Finish STM32 digital interface assignment
2021-12-08 Add multiplexing MCU and USB
2021-12-08 Add tag connect programming/debug interface
2021-12-10 Add mounting pad for safety pin
2021-12-10 Make space for STM32
2021-12-11 Route ESP32 SPI bus
2021-12-11 Add preliminary ESP32 power layout
2021-12-11 Layout horizontal busses
2021-12-11 Layout 3V3 buck/boost converter
2021-12-11 Implement power path
2021-12-11 Connect SWD to USB type C SBU
2021-12-11 Wire column mux SPI
2021-12-11 Layout remaining busses
2021-12-11 Add primary battery protection
2021-12-11 Finish layout
2021-12-11 Connect charger state outputs to STM32
2021-12-11 Add pin1 markers
2021-12-11 Fix DRC errors
2021-12-11 Fix missaligned SWD testpoints
2021-12-11 Add silkscreen markings
2021-12-12 Use better ESP32 Pico D4 footprint
2021-12-12 Hide U24 silkscreen designator again
2021-12-12 Fix mounting type of SMT components
2021-12-12 Add 3d models
2021-12-12 Add 3d model to VBUS enable inverter
2021-12-13 Add DCDC inductor 3D model
2021-12-14 Add a nicer safety pin 3D model
2021-12-17 Improve layout
2021-12-17 More layout improvements
2021-12-17 Stitch L1 GND together on L2
2021-12-17 Patch up L1 GND even more
2021-12-17 Improve VBUS connectivity
2021-12-17 Add more GND via stitching
2021-12-17 Improve ESP32 3V3 power routing
2021-12-18 Improve VBUS impedance to high side drivers
2021-12-18 Add additional VBUS bulk capacitance
2021-12-20 Give Alps SKRK switch 3D model natural colors
2021-12-20 Add fuel gauge
2021-12-20 Improve BATT+ connectivity on main DC/DC
2021-12-23 Align DC/DC pin 1 indicator
2021-12-27 Fix 5.1k resistor package
2021-12-27 Connect ESD diode after SWD SBU resistors
2021-12-27 Fix row/column misnomer
    The row/column terms were swapped. The high side drivers control columns
    while the low side drivers switch the rows.
2021-12-27 Implement USB type C SWDIO SBU changes
2021-12-30 Add 16MHz crystal
    Turns out the STM32F7 DFU bootloader uses the HSE for USB clocking and
    thus requires a crystal. No fallback to HSI is implemented. *sigh*
2021-12-30 Improce +3V3 routing for less wiggles
2021-12-30 Right align year of design with my surname
2021-12-30 Remove stray piece of trace on main DC/DC
2021-12-30 Add solder paste definition to led panel contact pads
2021-12-30 Use new led panel footprint
2021-12-31 Add missing part references
2022-01-15 Clean up schematic
2022-01-15 Add schematic export
2022-01-15 Add license
2022-01-15 Add README
2022-01-15 Add note on assembly
2022-01-15 Fix flipped x/y dimensions
2022-01-15 Add fireworks animation to readme
2022-01-15 Fix typo
2022-01-15 Update schematic to include title block
2022-03-18 Add simple 3d printable case
2023-04-07 Add high fidelity led panel 3d model
